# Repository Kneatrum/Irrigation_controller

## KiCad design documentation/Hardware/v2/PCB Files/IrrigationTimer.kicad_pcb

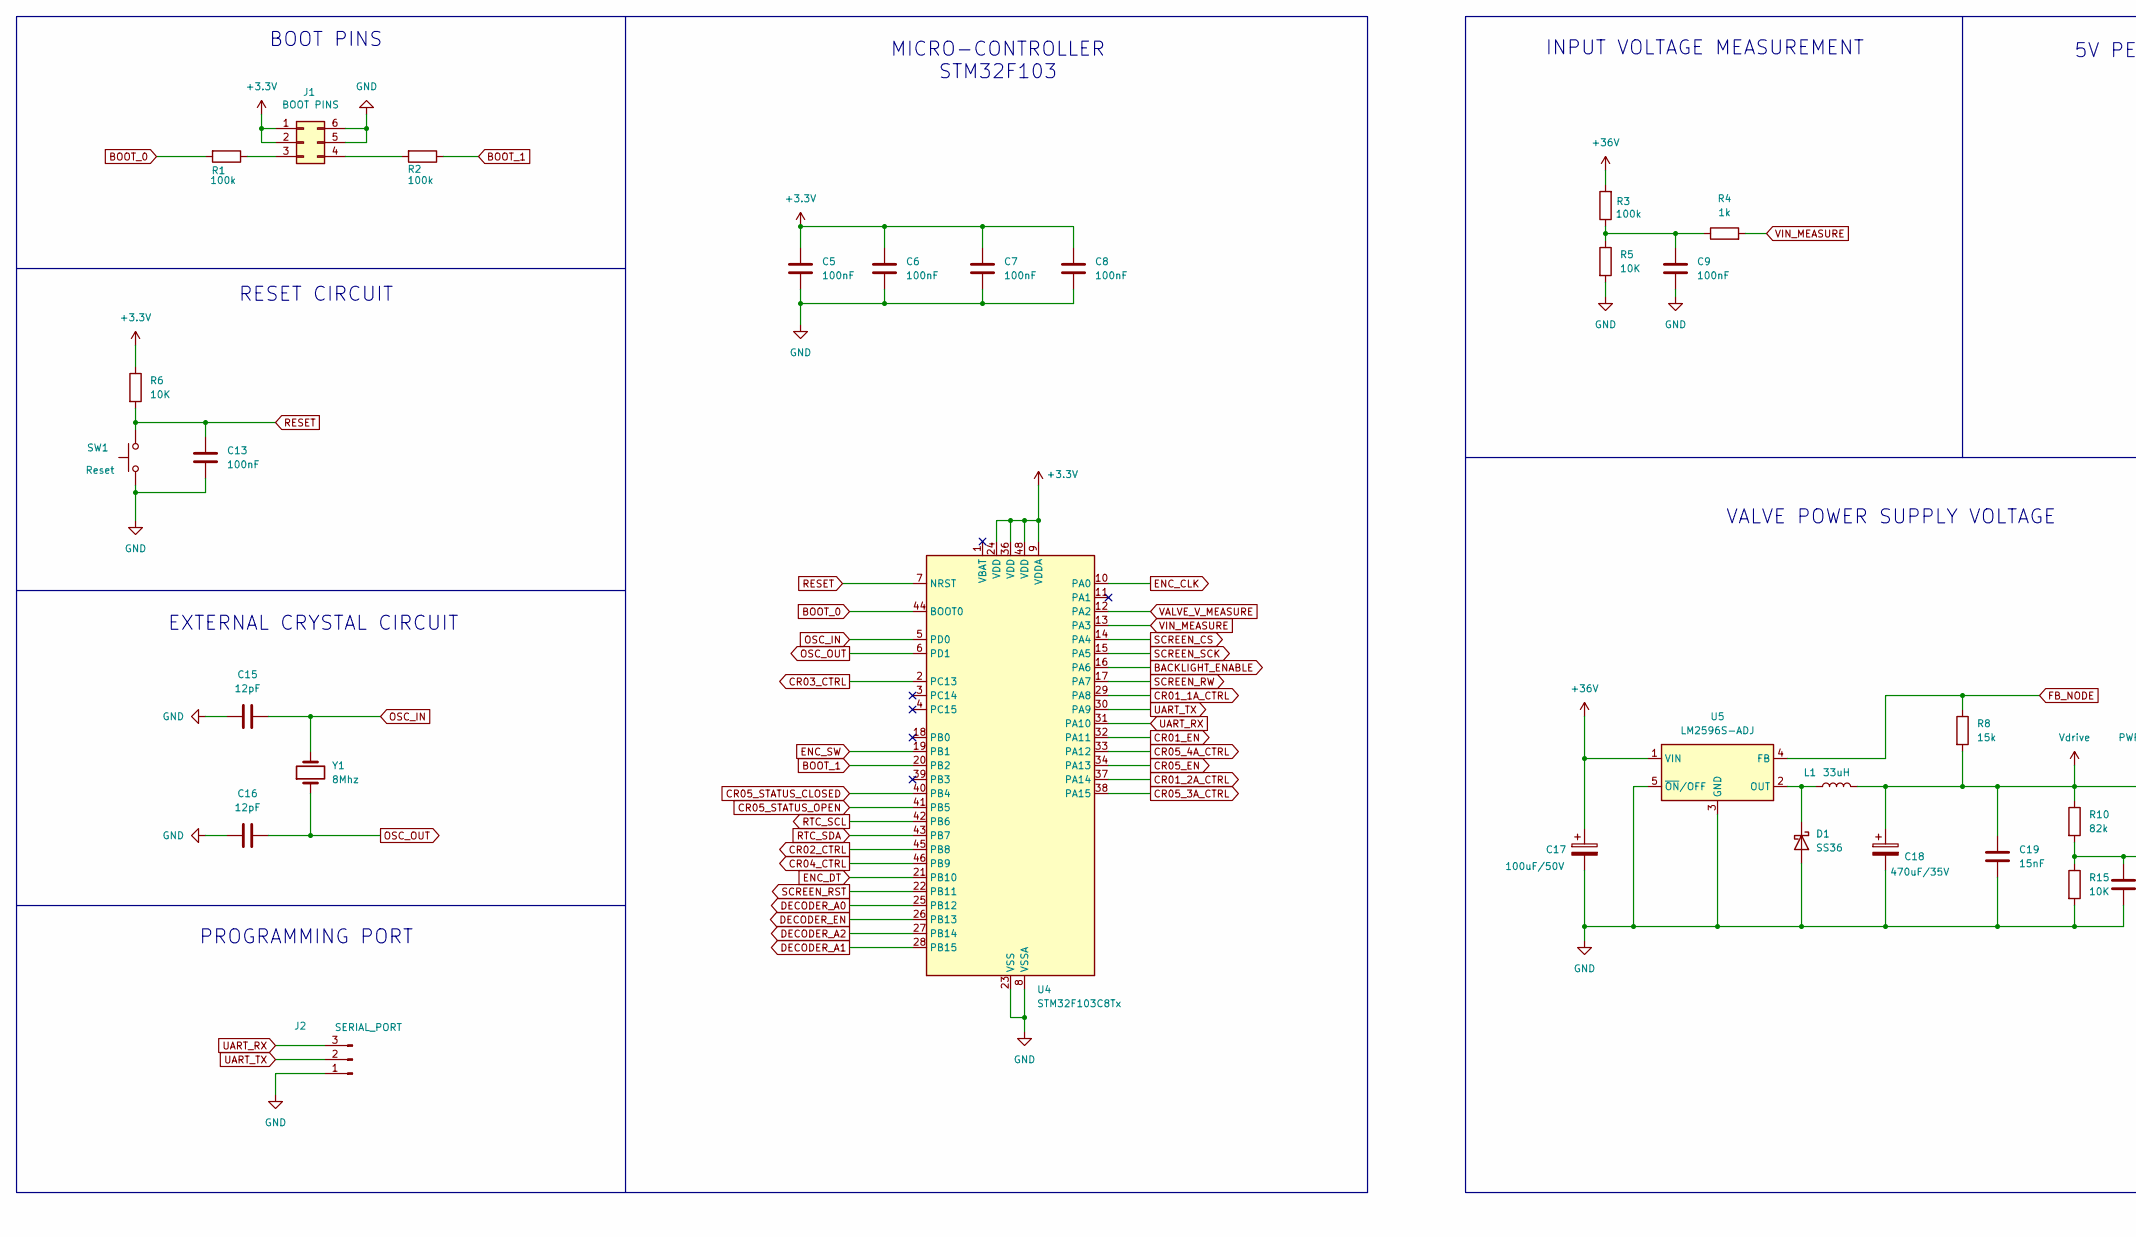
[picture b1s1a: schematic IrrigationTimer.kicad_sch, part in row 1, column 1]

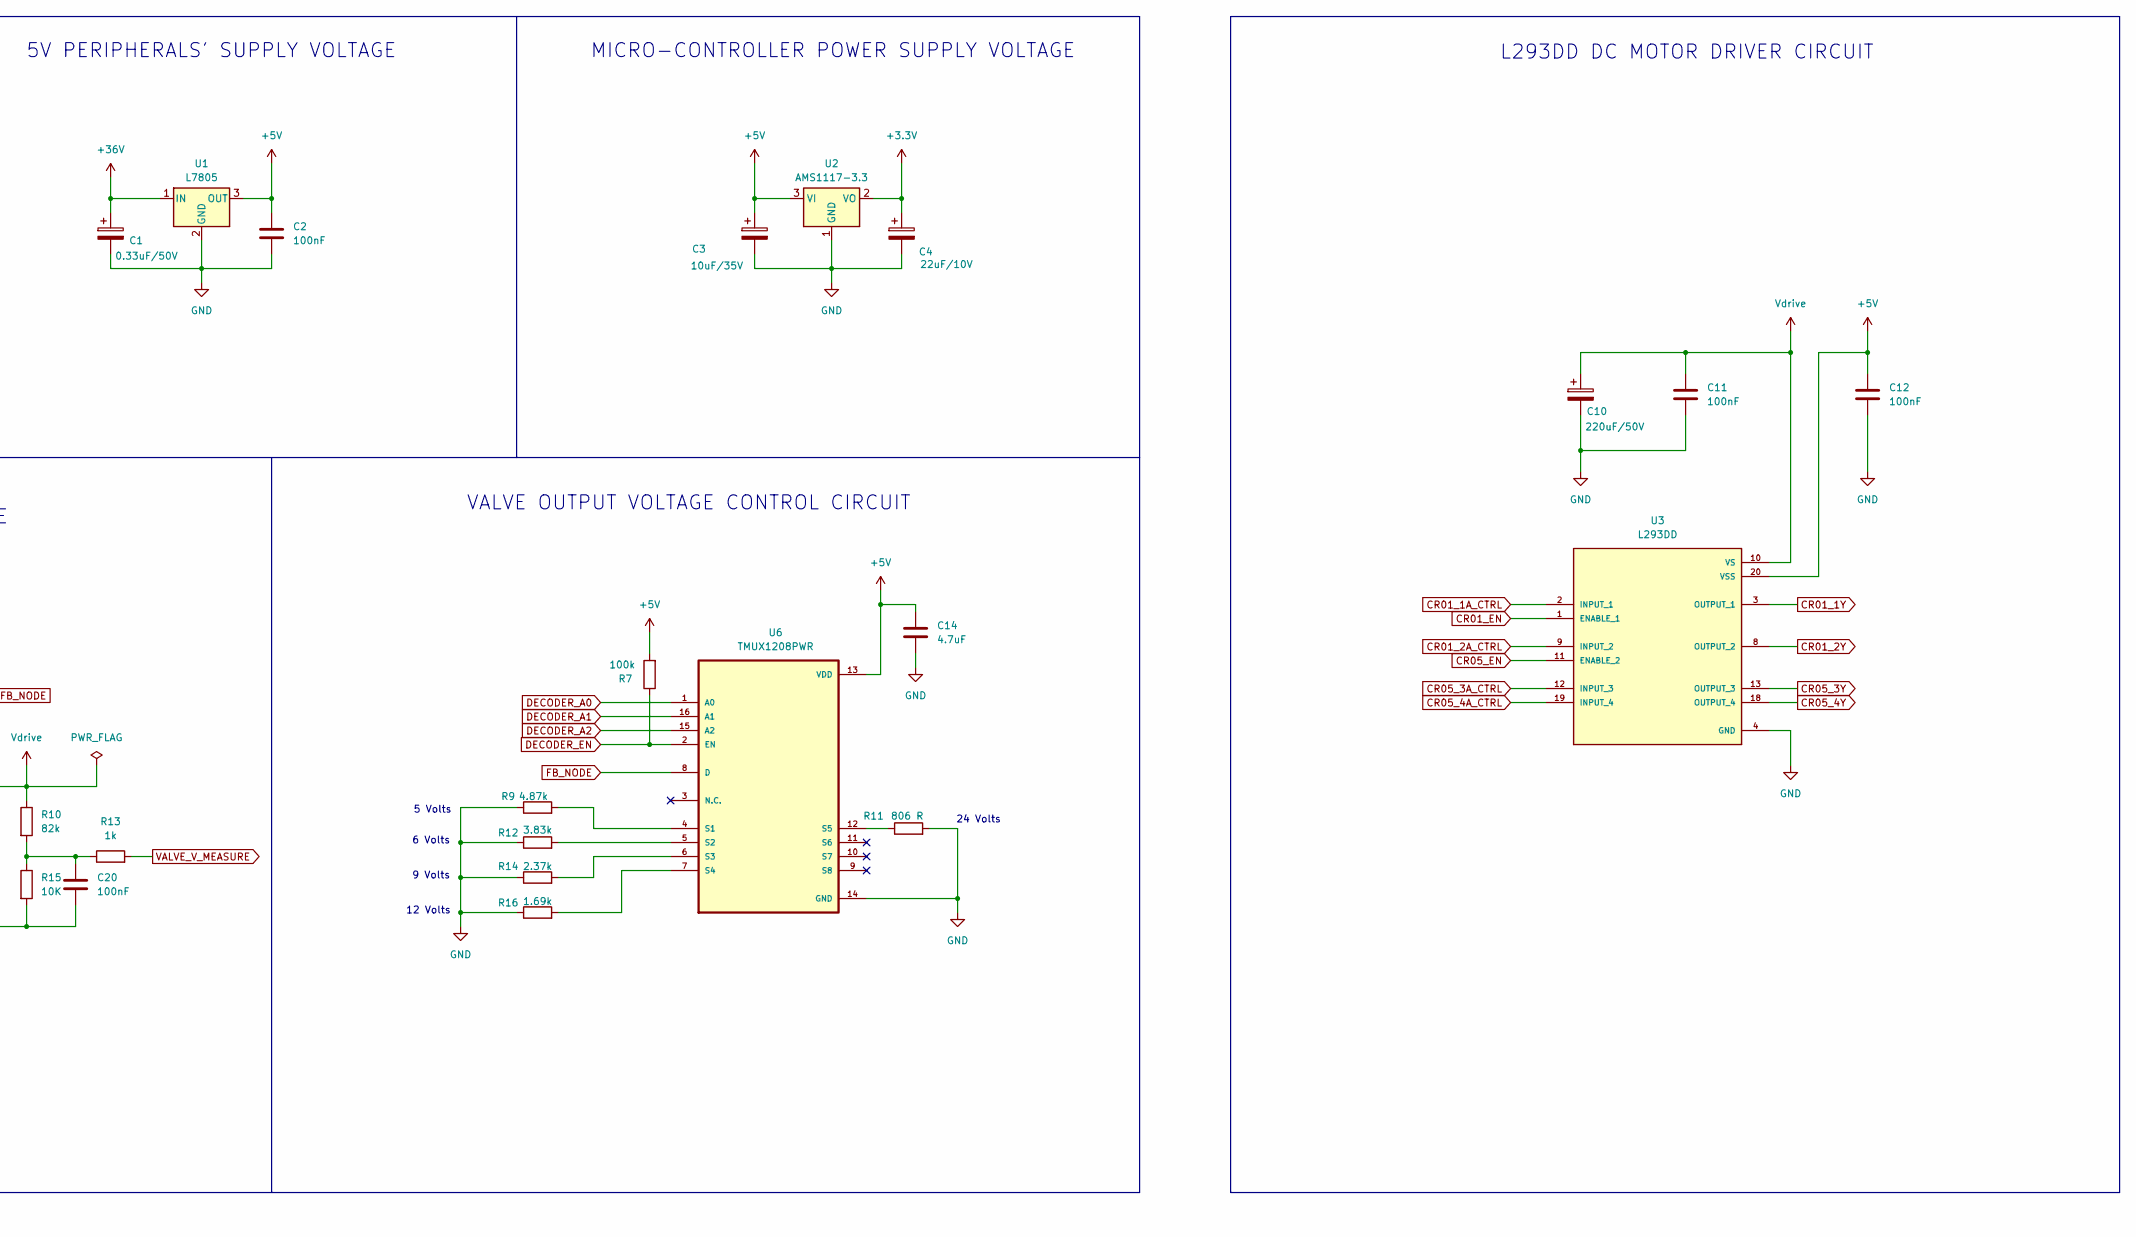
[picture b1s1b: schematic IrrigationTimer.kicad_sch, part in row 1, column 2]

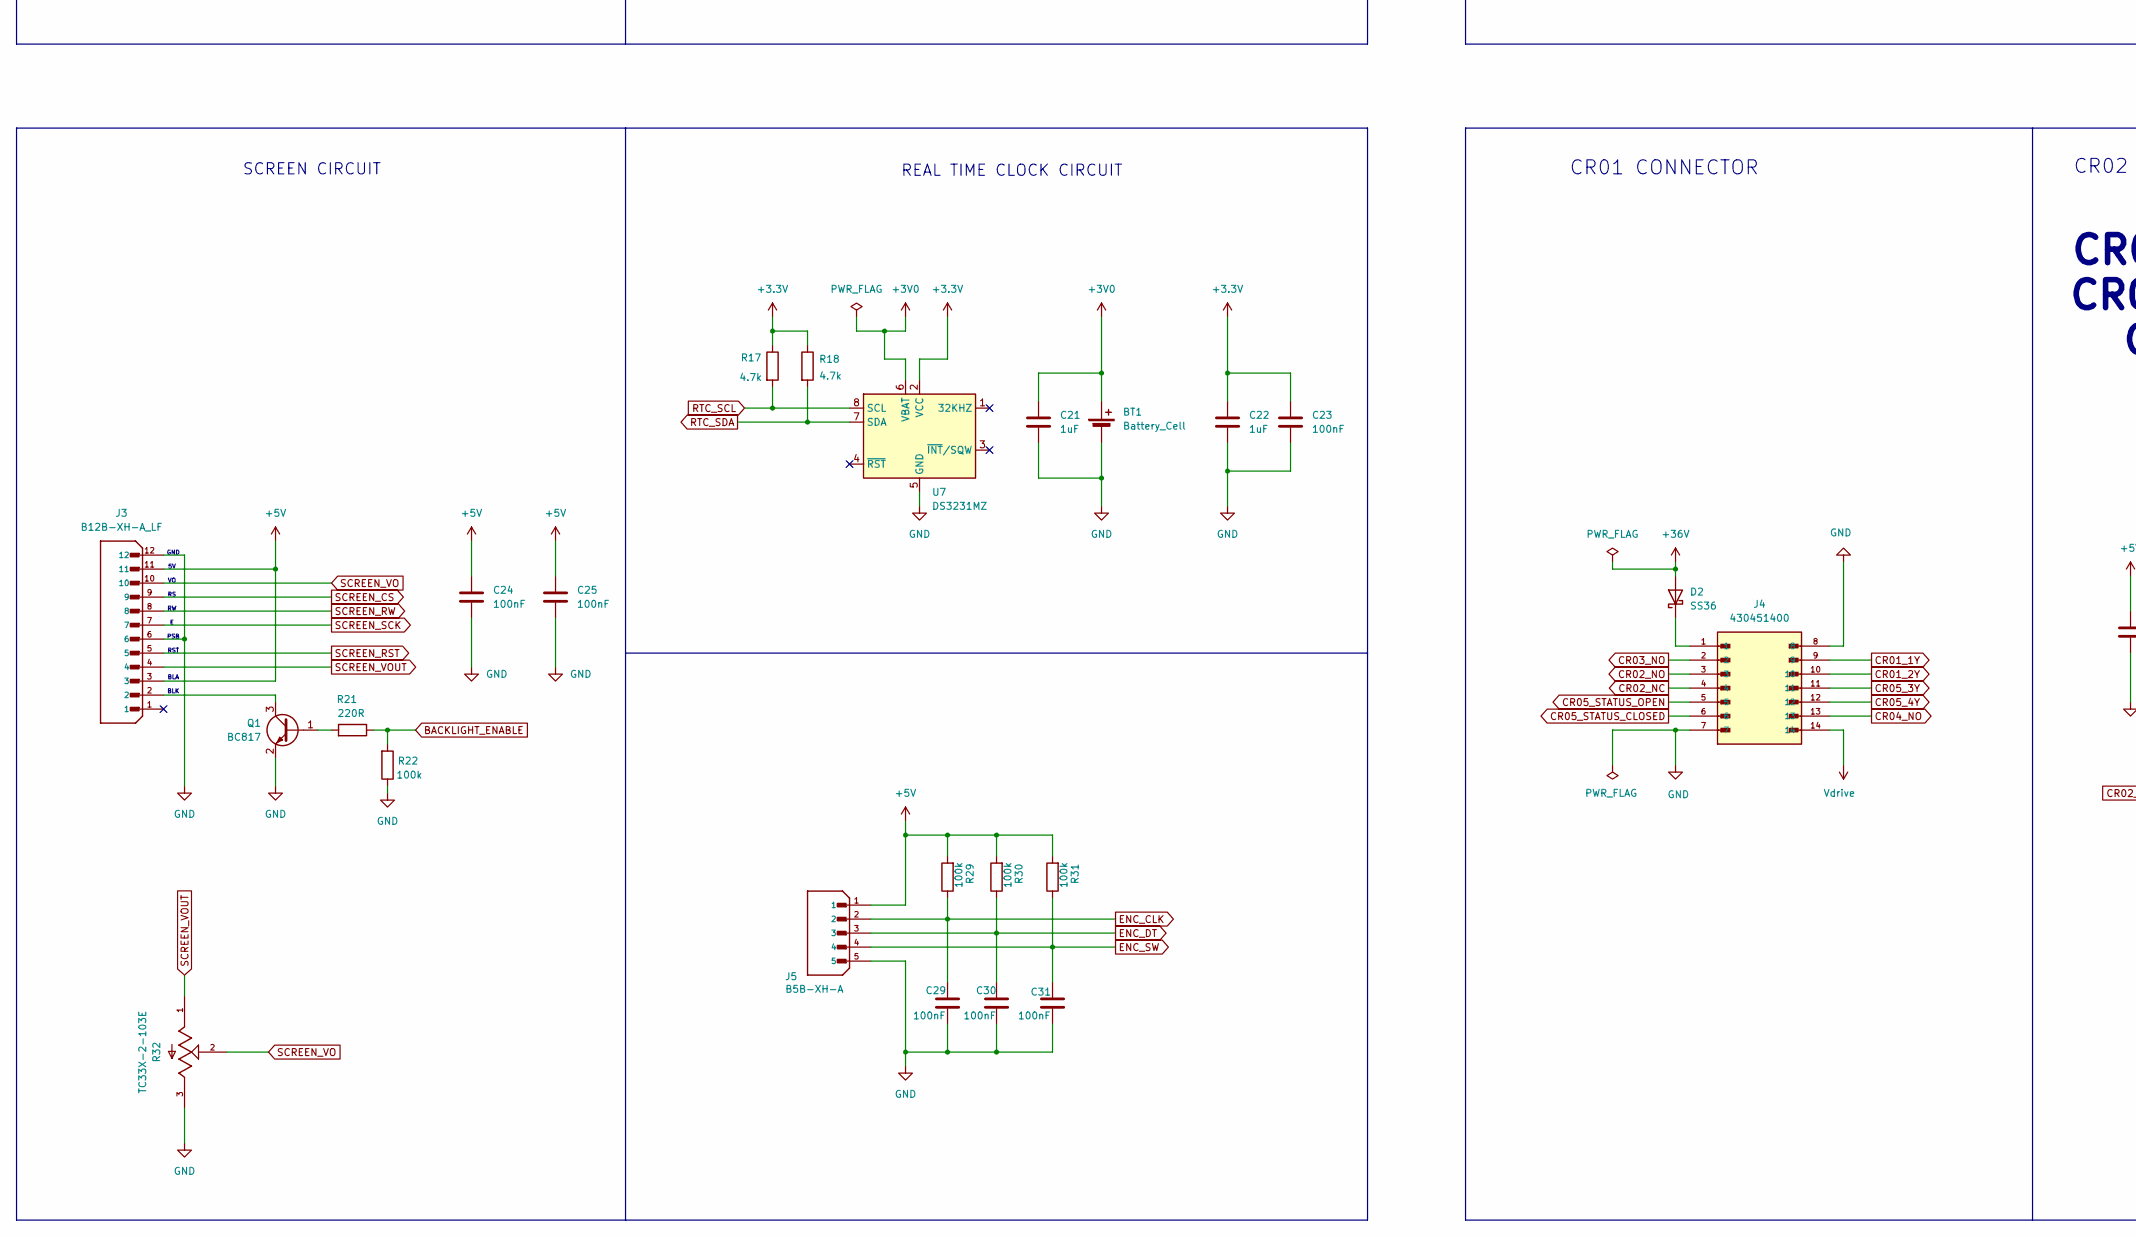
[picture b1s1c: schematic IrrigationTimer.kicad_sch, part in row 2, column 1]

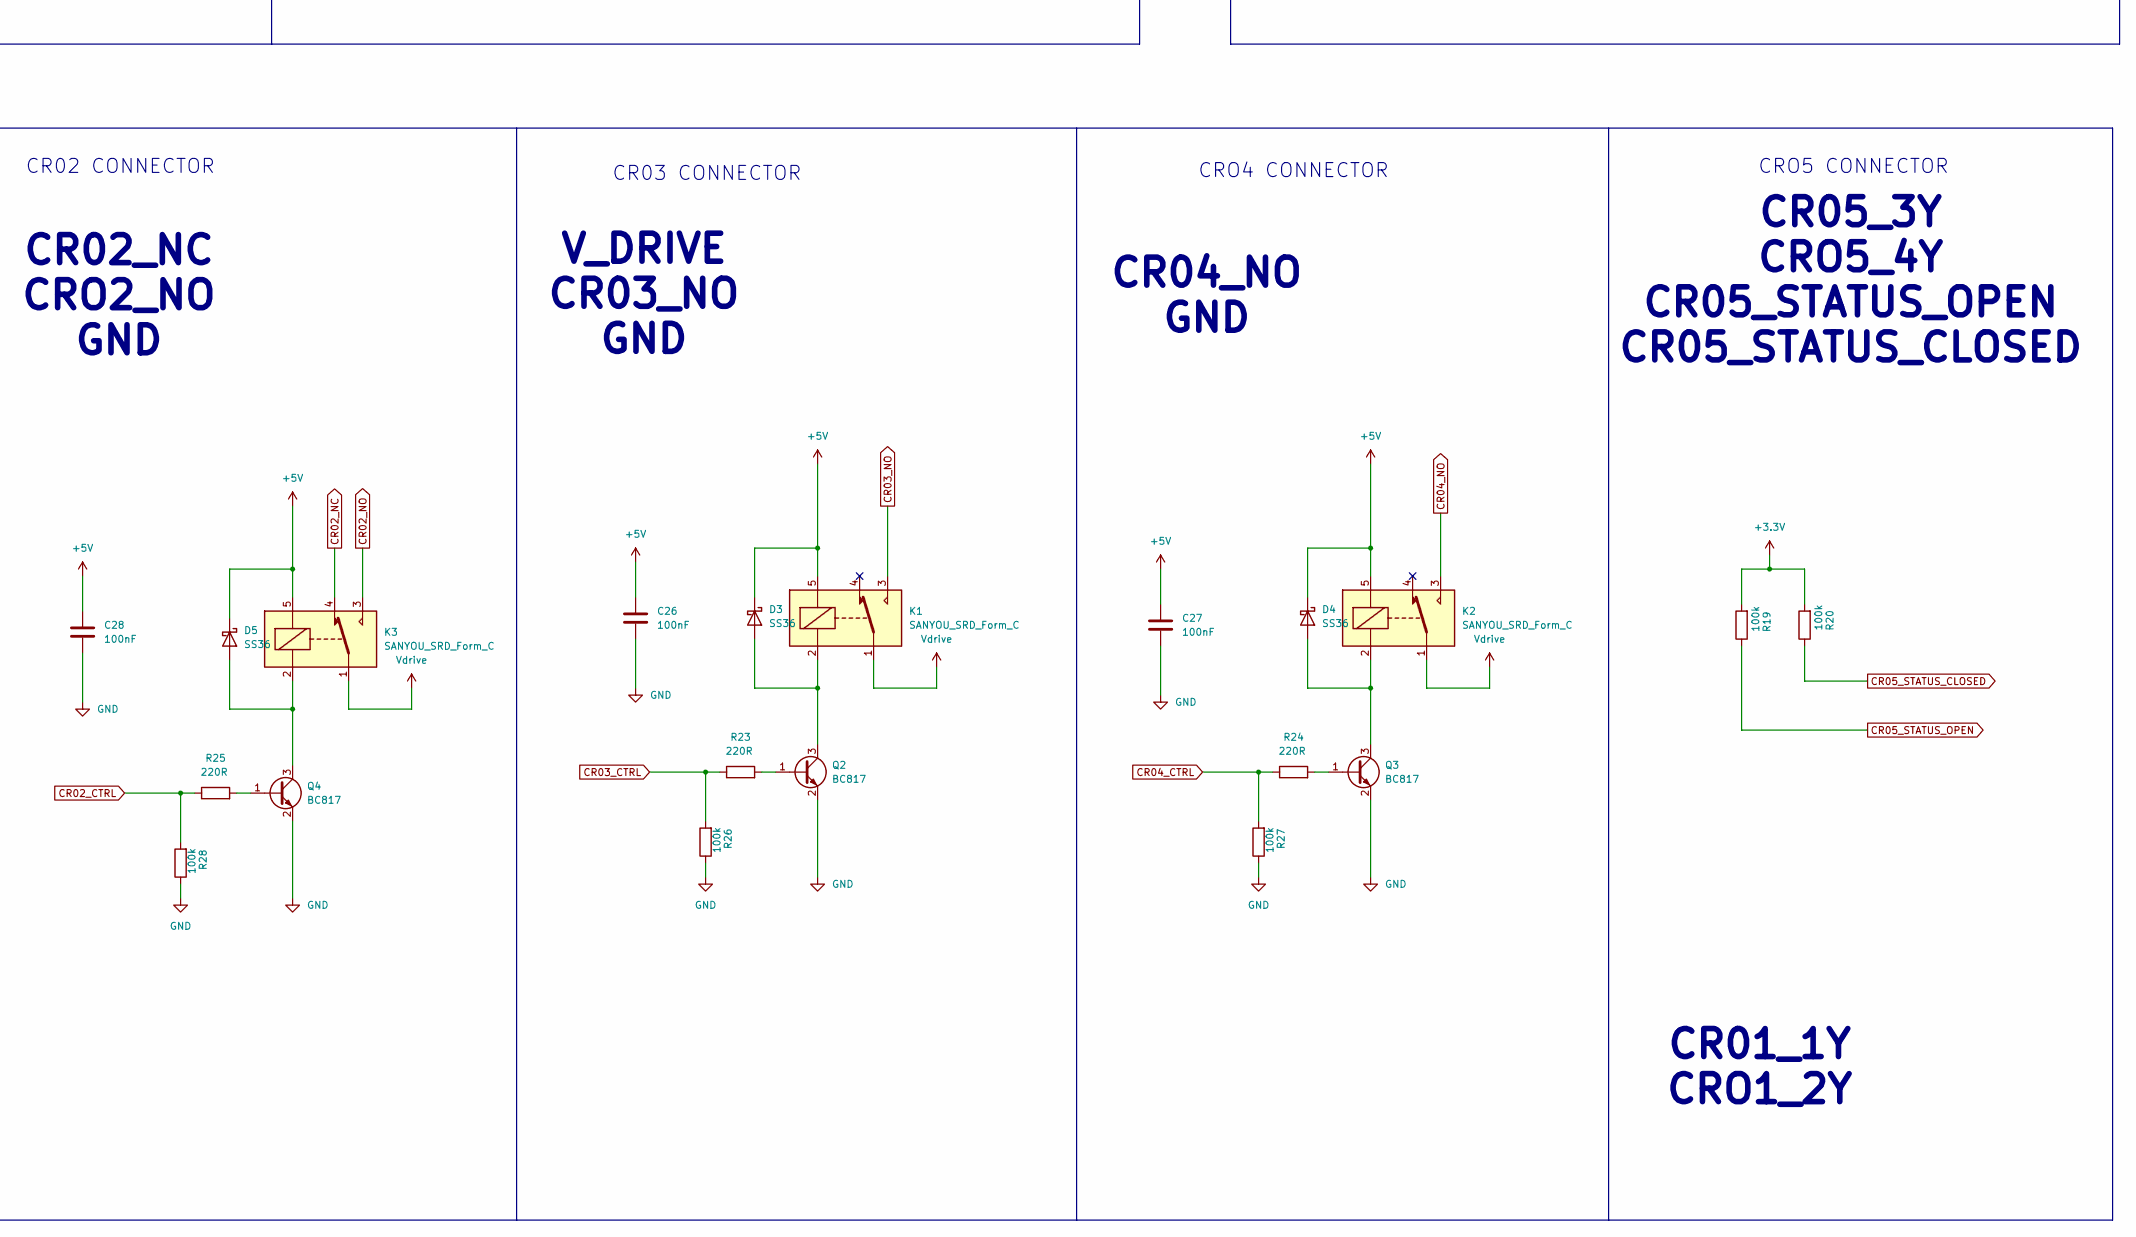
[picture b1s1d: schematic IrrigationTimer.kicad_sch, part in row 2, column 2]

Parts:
BT1: Battery_Cell; BatteryHolder_MYOUNG_BS-07-A1BJ001_CR2032
C1: 0.33uF/50V; CP_Elec_4x5.4; LCSC PN C264238
C2, C5, C6, C7, C8, C9, C11, C12, C13, C20, C23, C24, C25, C26, C27, C28, C29, C30, C31: 100nF; C_0805_2012Metric; LCSC PN C1711
C3: 10uF/35V; CP_Elec_4x5.4; LCSC PN C4747970
C4: 22uF/10V; CP_Elec_4x5.4; LCSC PN C48970747
C10: 220uF/50V; CP_Elec_10x10.5; LCSC C970698
C14: 4.7uF; C_0805_2012Metric; LCSC PN C98192
C15, C16: 12pF; C_0805_2012Metric; LCSC PN C107108
C17: 100uF/50V; CP_Elec_8x10; LCSC PN C2836439
C18: 470uF/35V; CP_Elec_10x12.5; LCSC PN C22469994
C19: 15nF; C_0805_2012Metric; LCSC PN C445728
C21, C22: 1uF; C_0805_2012Metric; LCSC PN C28323
D1, D2, D3, D4, D5: SS36; D_SMA; LCSC PN C3014012
J1: BOOT PINS; PinHeader_2x03_P2.54mm_Vertical_SMD; LCSC PN C32713283
J2: SERIAL_PORT; PinHeader_1x03_P2.54mm_Vertical; LCSC PN C52016391
J3: B12B-XH-A_LF; JST_B12B-XH-A_LF__SN_; PARTREV 7/4/21; LCSC PN C52121892
J4: 430451400; MOLEX_430451400; PARTREV G; LCSC PN C22383229
J5: B5B-XH-A; JST_B5B-XH-A; PARTREV 7/4/21; LCSC PN C157991
K1, K2, K3: SANYOU_SRD_Form_C; Relay_SPDT_SANYOU_SRD_Series_Form_C; LCSC PN C35449
L1: 33uH; L_12x12mm_H8mm; LCSC PN C9400
Q1, Q2, Q3, Q4: BC817; SOT-23; LCSC PN C49238158
R1, R2, R3, R7, R19, R20, R22, R26, R27, R28, R29, R30, R31: 100k; R_0805_2012Metric; LCSC PN C2907293
R4, R13: 1k; R_0805_2012Metric; LCSC PN C2907232
R5, R6, R15: 10K; R_0805_2012Metric; LCSC PN C2907219
R8: 15k; R_0805_2012Metric; LCSC PN C2930170
R9: 4.87k; R_0805_2012Metric; LCSC PN C2930197
R10: 82k; R_0805_2012Metric; LCSC PN C17840
R11: 806 R; R_0805_2012Metric; LCSC PN C2999620
R12: 3.83k; R_0805_2012Metric; LCSC PN C2933428
R14: 2.37k; R_0805_2012Metric; LCSC PN C5126005
R16: 1.69k; R_0805_2012Metric; LCSC PN C2482737
R17, R18: 4.7k; R_0805_2012Metric; LCSC PN C2907326
R21, R23, R24, R25: 220R; R_0805_2012Metric; LCSC PN C17557
R32: TC33X-2-103E; TRIM_TC33X-2-103E; LCSC PN C719176
SW1: Reset; SW_Push_1P1T_XKB_TS-1187A; LCSC PN C318884
U1: L7805; TO-252-2; LCSC C42376985
U2: AMS1117-3.3; SOT-223-3_TabPin2; LCSC PN C5205141
U3: L293DD; SOIC127P1032X265-20N; LCSC PN C2973803
U4: STM32F103C8Tx; LQFP-48_7x7mm_P0.5mm; LCSC PN C8734
U5: LM2596S-ADJ; TO-263-5_TabPin3; LCSC PN C5276751
U6: TMUX1208PWR; SOP65P640X120-16N; LCSC PN C494728
U7: DS3231MZ; SOIC-8_3.9x4.9mm_P1.27mm; LCSC PN C107410
Y1: 8Mhz; Crystal_SMD_HC49-SD; LCSC PN C5265803

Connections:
+3.3V: C4.1, C5.1, C6.1, C7.1, C8.1, C22.1, C23.1, J1.1, J1.2, R6.1, R17.1, R18.1, R19.2, R20.2, U2.2 (VO), U4.9 (VDDA), U4.24 (VDD), U4.36 (VDD), U4.48 (VDD), U7.2 (VCC)
+3V0: BT1.1 (+), C21.1, U7.6 (VBAT)
+5V: C2.1, C3.1, C12.1, C14.1, C24.1, C25.1, C26.1, C27.1, C28.1, D3.1 (K), D4.1 (K), D5.1 (K), J3.3, J3.11, J5.1, K1.5, K2.5, K3.5, R7.2, R29.2, R30.2, R31.2, U1.3 (OUT), U2.3 (VI), U3.20 (VSS), U6.13 (VDD)
+36V: C1.1, C17.1, D2.2 (A), R3.2, U1.1 (IN), U5.1 (VIN)
BACKLIGHT_ENABLE: R21.1, R22.2, U4.16 (PA6)
BOOT_0: R1.2, U4.44 (BOOT0)
BOOT_1: R2.1, U4.20 (PB2)
CR01_1A_CTRL: U3.2 (INPUT_1), U4.29 (PA8)
CR01_1Y: J4.9, U3.3 (OUTPUT_1)
CR01_2A_CTRL: U3.9 (INPUT_2), U4.37 (PA14)
CR01_2Y: J4.10, U3.8 (OUTPUT_2)
CR01_EN: U3.1 (ENABLE_1), U4.32 (PA11)
CR02_CTRL: R25.1, R28.2, U4.45 (PB8)
CR02_NC: J4.4, K3.4
CR02_NO: J4.3, K3.3
CR03_CTRL: R23.1, R26.2, U4.2 (PC13)
CR03_NO: J4.2, K1.3
CR04_CTRL: R24.1, R27.2, U4.46 (PB9)
CR04_NO: J4.13, K2.3
CR05_3A_CTRL: U3.12 (INPUT_3), U4.38 (PA15)
CR05_3Y: J4.11, U3.13 (OUTPUT_3)
CR05_4A_CTRL: U3.19 (INPUT_4), U4.33 (PA12)
CR05_4Y: J4.12, U3.18 (OUTPUT_4)
CR05_EN: U3.11 (ENABLE_2), U4.34 (PA13)
CR05_STATUS_CLOSED: J4.6, R20.1, U4.40 (PB4)
CR05_STATUS_OPEN: J4.5, R19.1, U4.41 (PB5)
DECODER_A0: U4.25 (PB12), U6.1 (A0)
DECODER_A1: U4.28 (PB15), U6.16 (A1)
DECODER_A2: U4.27 (PB14), U6.15 (A2)
DECODER_EN: R7.1, U4.26 (PB13), U6.2 (EN)
ENC_CLK: C29.1, J5.2, R29.1, U4.10 (PA0)
ENC_DT: C30.1, J5.3, R30.1, U4.21 (PB10)
ENC_SW: C31.1, J5.4, R31.1, U4.19 (PB1)
FB_NODE: R8.1, U5.4 (FB), U6.8 (D)
GND: BT1.2 (-), C1.2, C2.2, C3.2, C4.2, C5.2, C6.2, C7.2, C8.2, C9.2, C10.2, C11.2, C12.2, C13.2, C14.2, C15.1, C16.1, C17.2, C18.2, C19.2, C20.2, C21.2, C22.2, C23.2, C24.2, C25.2, C26.2, C27.2, C28.2, C29.2, C30.2, C31.2, D1.2 (A), J1.5, J1.6, J2.1, J3.6, J3.12, J4.7, J4.8, J5.5, Q1.2 (E), Q2.2 (E), Q3.2 (E), Q4.2 (E), R5.2, R9.1, R11.2, R12.1, R14.1, R15.2, R16.1, R22.1, R26.1, R27.1, R28.1, R32.3, SW1.1, U1.2 (GND), U2.1 (GND), U3.4 (GND), U3.5 (GND), U3.6 (GND), U3.7 (GND), U3.14 (GND), U3.15 (GND), U3.16 (GND), U3.17 (GND), U4.8 (VSSA), U4.23 (VSS), U4.35 (VSS), U4.47 (VSS), U5.3 (GND), U5.5 (~ON/OFF), U6.14 (GND), U7.5 (GND)
unnamed: C9.1, R3.1, R4.1, R5.1
unnamed: C20.1, R10.2, R13.1, R15.1
unnamed: D1.1 (K), L1.1, U5.2 (OUT)
unnamed: D2.1 (K), J4.1
unnamed: D3.2 (A), K1.2, Q2.3 (C)
unnamed: D4.2 (A), K2.2, Q3.3 (C)
unnamed: D5.2 (A), K3.2, Q4.3 (C)
unnamed: J1.3, R1.1
unnamed: J1.4, R2.2
unnamed: Q1.1 (B), R21.2
unnamed: J3.2, Q1.3 (C)
unnamed: Q2.1 (B), R23.2
unnamed: Q3.1 (B), R24.2
unnamed: Q4.1 (B), R25.2
unnamed: R9.2, U6.4 (S1)
unnamed: R12.2, U6.5 (S2)
unnamed: R14.2, U6.6 (S3)
unnamed: R16.2, U6.7 (S4)
unnamed: R11.1, U6.12 (S5)
OSC_IN: C15.2, U4.5 (PD0), Y1.2
OSC_OUT: C16.2, U4.6 (PD1), Y1.1
RESET: C13.1, R6.2, SW1.2, U4.7 (NRST)
RTC_SCL: R17.2, U4.42 (PB6), U7.8 (SCL)
RTC_SDA: R18.2, U4.43 (PB7), U7.7 (SDA)
SCREEN_CS: J3.9, U4.14 (PA4)
SCREEN_RST: J3.5, U4.22 (PB11)
SCREEN_RW: J3.8, U4.17 (PA7)
SCREEN_SCK: J3.7, U4.15 (PA5)
SCREEN_VO: J3.10, R32.2
SCREEN_VOUT: J3.4, R32.1
UART_RX: J2.3, U4.31 (PA10)
UART_TX: J2.2, U4.30 (PA9)
VALVE_V_MEASURE: R13.2, U4.12 (PA2)
VIN_MEASURE: R4.2, U4.13 (PA3)
Vdrive: C10.1, C11.1, C18.1, C19.1, J4.14, K1.1, K2.1, K3.1, L1.2, R8.2, R10.1, U3.10 (VS)

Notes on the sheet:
INPUT VOLTAGE MEASUREMENT
L293DD DC MOTOR DRIVER CIRCUIT
RST
12 Volts
CR01_1Y CRO1_2Y
VALVE OUTPUT VOLTAGE CONTROL CIRCUIT
6 Volts
CR05_3Y CRO5_4Y CR05_STATUS_OPEN CR05_STATUS_CLOSED
MICRO-CONTROLLER STM32F103
CRO5 CONNECTOR
REAL TIME CLOCK CIRCUIT
CR04_NO GND
SCREEN CIRCUIT
BOOT PINS
5 Volts
BLK
CR02 CONNECTOR
CR01 CONNECTOR
VALVE POWER SUPPLY VOLTAGE
9 Volts
GND
CR02_NC CRO2_NO GND
MICRO-CONTROLLER POWER SUPPLY VOLTAGE
24 Volts
BLA
V_DRIVE CR03_NO GND
5V PERIPHERALS' SUPPLY VOLTAGE
CR03 CONNECTOR
RESET CIRCUIT
PROGRAMMING PORT
CRO4 CONNECTOR
EXTERNAL CRYSTAL CIRCUIT
PSB

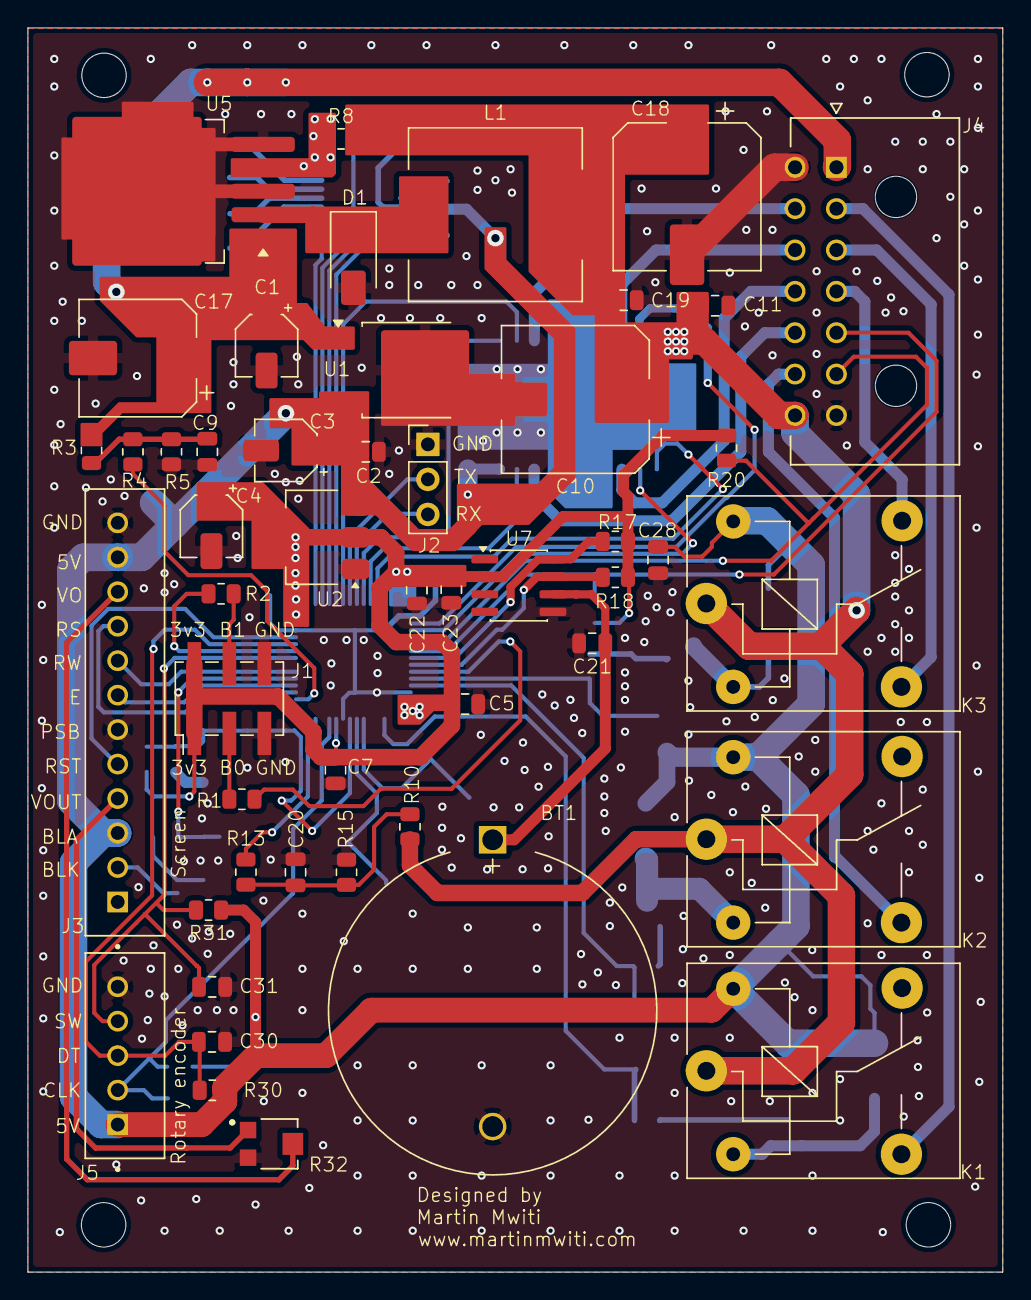
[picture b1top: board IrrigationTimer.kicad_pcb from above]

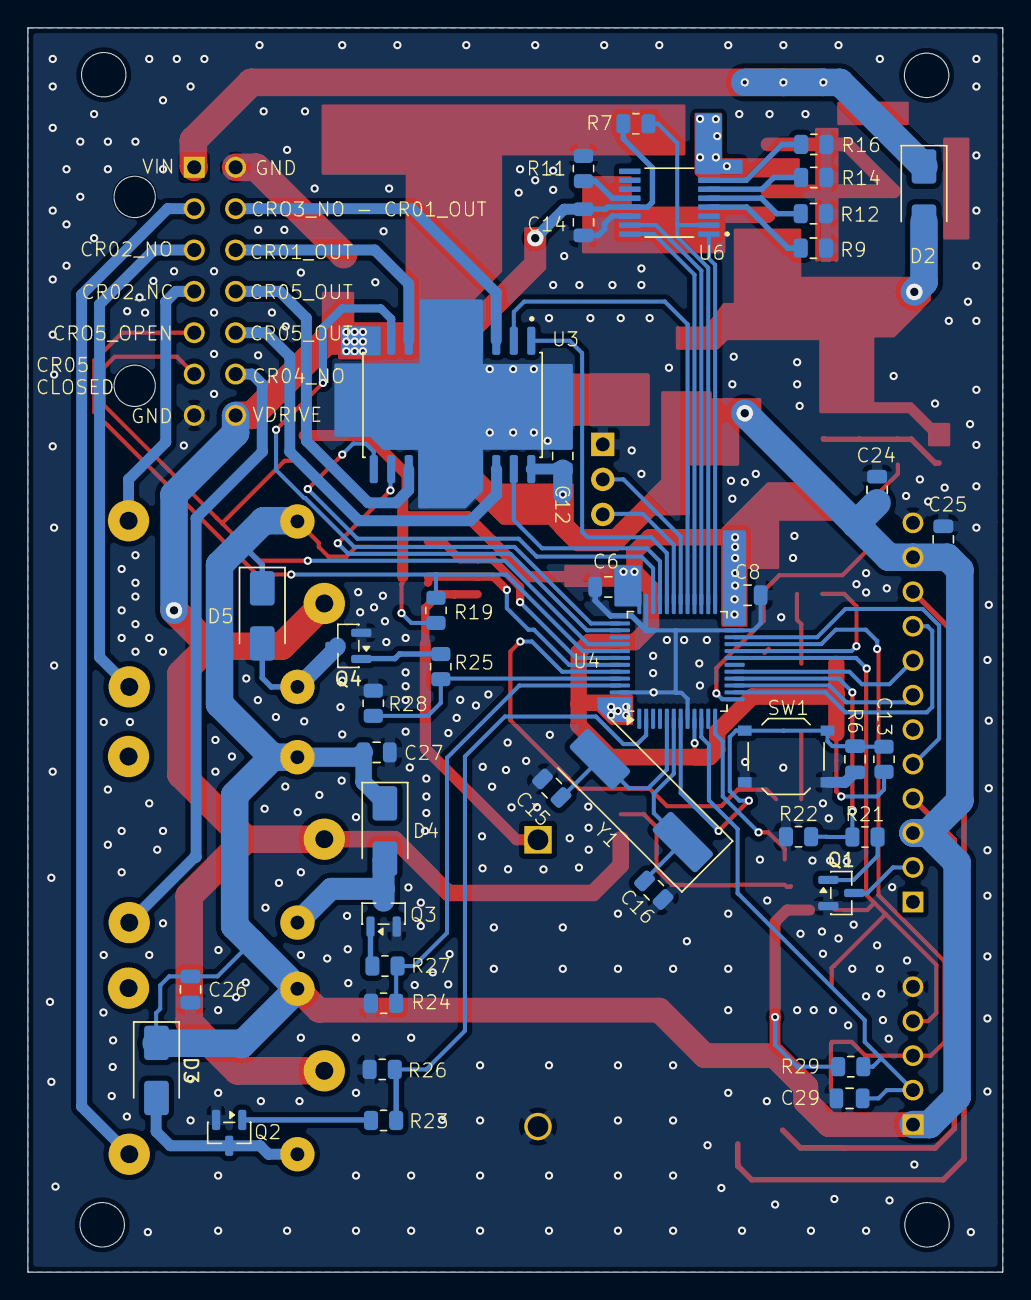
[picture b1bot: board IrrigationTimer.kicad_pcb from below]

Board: 2 copper layers, 70.7 x 90.2 mm, 91 parts (42 on the bottom side), 70 nets.

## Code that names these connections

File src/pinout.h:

#ifndef PINOUT_H
#define PINOUT_H

// I2C communication pins
#define I2C_SDA_PIN PB7
#define I2C_SCL_PIN PB6

// SPI communication pins for GLCD 
#define PIN_SCK  PA5
#define PIN_MOSI PA7
#define PIN_CS   PA4
#define PIN_RST  PB11

// Screen backlight pin
#define BACKLIGHT_PIN PA6  // Change this to another non-spi pin and leave it unused.

// Relay control pins
#define CR02_CTRL PB8 
#define CR03_CTRL PC13 
#define CR04_CTRL PB9 

// Rotary encoder pins
#define ROTARY_ENCODER_CLK_PIN PB10
#define ROTARY_ENCODER_DT_PIN  PA0
#define ROTARY_ENCODER_SW_PIN  PB1

// Analog multiplexer pins.
#define TMUX_1208_EN_PIN PB13
#define TMUX_1208_A0_PIN PB12
#define TMUX_1208_A1_PIN PB15
#define TMUX_1208_A2_PIN PB14

// Motor driver pins
#define CR01_EN       PA11
#define CR05_EN       PA13
#define CR01_1A_CTRL  PA8
#define CR01_2A_CTRL  PA14
#define CR05_3A_CTRL  PA15
#define CR05_4A_CTRL  PA12

// CR05 status feedback pin
#define CR05_STATUS_CLOSED PB4
#define CR05_STATUS_OPEN   PB5

// Analog pins
#define VALVE_V_MEASURE_PIN PA2
#define VIN_MEASURE_PIN     PA3

#endif

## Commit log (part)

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2025-11-15 Improve button press functionality and add a long press detection
2025-11-15 Detach encoder DT pin from interrupt
2025-11-16 Add state related variables into stateMachine and handle resetting in functions
2025-11-16 Apply stateMachine changes
2025-11-16 Handle resetting of states
2025-11-16 Set up a prompt for user to confirm irrigation schedule changes
2025-11-16 Handle irrigation schedule changes
2025-11-16 Implement logic for long press operations
2025-11-16 Apply changes to stateMachine
2025-11-16 Implement logic for skipping "Force Stop" when valve is closed
2025-11-16 Reset timers when button is pressed
2025-11-16 Set lower and upper limits for the year field
2025-11-16 Create a prompt for the user to accept time settings
2025-11-16 Implement saving time settings
2025-11-16 Refactor showSystemTimeSetting function
2025-11-16 Refactor setSystemTime
2025-11-16 Refactor RTCTime_t and getRTCTime()
2025-11-16 Add a function for validating days of the months
2025-11-16 Refactor handleSystemTimeField
2025-11-16 Refactor configureSystemTime
2025-11-16 Prevent time updates when setting time
2025-11-16 Change display format
2025-11-16 Remove print statement
2025-11-16 Write functions for saving force_stop status into eeprom
2025-11-16 Refactor drawMenu function
2025-11-16 Refactor showDetailsScreen function
2025-11-16 Add force_stop and valve_on into stateMachine struct
2025-11-16 Add force_stop and valve_on to stateMachine struct
2025-11-16 Add a function for printing the state machine struct
2025-11-16 Update valve_on state after turning it on or off
2025-11-16 Minor changes
2025-11-16 Implement the force_stop functionality
2025-11-16 Minor change
2025-11-16 Go back to showing details after forcing or resuming irrigation
2025-11-16 Reverse turning direction
2025-11-17 Minor changes to text displayed on screen
2025-11-17 Remove print statements
2026-04-17 Comment out Serial initialization in setup
2026-04-17 Add documentation files
2026-04-17 Add PCB files for Irrigation Timer v2 and LCSC order details
    - Created IrrigationTimer2.csv with component references, values, and quantities.
    - Added LCSC_ORDER.csv containing part numbers, manufacturer details, and pricing information for components used in the PCB design.
2026-04-17 Change from Arduino Micro to STM32f103
2026-04-17 Fix environment name formatting in platformio.ini
2026-04-17 Remove LiquidCrystal_I2C library dependency from platformio.ini
